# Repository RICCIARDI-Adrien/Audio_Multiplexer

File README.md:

# Audio multiplexer

## Description

A simple passive multiplexer providing :
* two 3.5mm jack inputs connected to two PC line outputs,
* two 3.5mm jack outputs connected to active speakers and a headset,
* one 3.5mm jack input connected to the headset microphone,
* two 3.5mm jack outputs connected to two PC microphone inputs.

```
                      +------+
             Line out |      | Mic in
     +----------------| PC 1 |<---------------+
     |                |      |                |
     |                +------+                |
     |                                        |
     |                +------+                |
     |       Line out |      | Mic in         |
     |   +------------| PC 2 |<-----------+   |
     |   |            |      |            |   |
     |   |            +------+            |   |
     |   |                                |   |
     v   v                                |   |
  +----------------------------------------------+             
  |              AUDIO MULTIPLEXER               |
  |                                              |
  |  Audio             Audio                Mic  |
  |   in                out                 in   |
  |                                              |
  +----------------------------------------------+
                       |  |                  ^
                       |  |                  |
                +------+  +-----+   +--------+
                |               |   |
                v               v   |
           +----------+      +---------+
           |          |      | Headset |
           | Speakers |      |  with   |
           |          |      |  mic    |
           +----------+      +---------+
```

The multiplexer microphone input is designed to be driven separately in case this is needed later.

## PCB

The PCB has been designed with KiCad 6.0.6.

Naked PCB :

Assembled PCB :

## Casing

The casing has been designed with FreeCAD 0.19. The multiple DXF files generated by FreeCAD have been combined using LibreCAD 2.1.3.
The casing has been designed to be laser-cut in a 4-mm thick 304 stainless steel.

Steel plates :

Casing top :

Casing bottom :

Casing front :

Casing rear :

Casing front angled :

Casing rear angled :

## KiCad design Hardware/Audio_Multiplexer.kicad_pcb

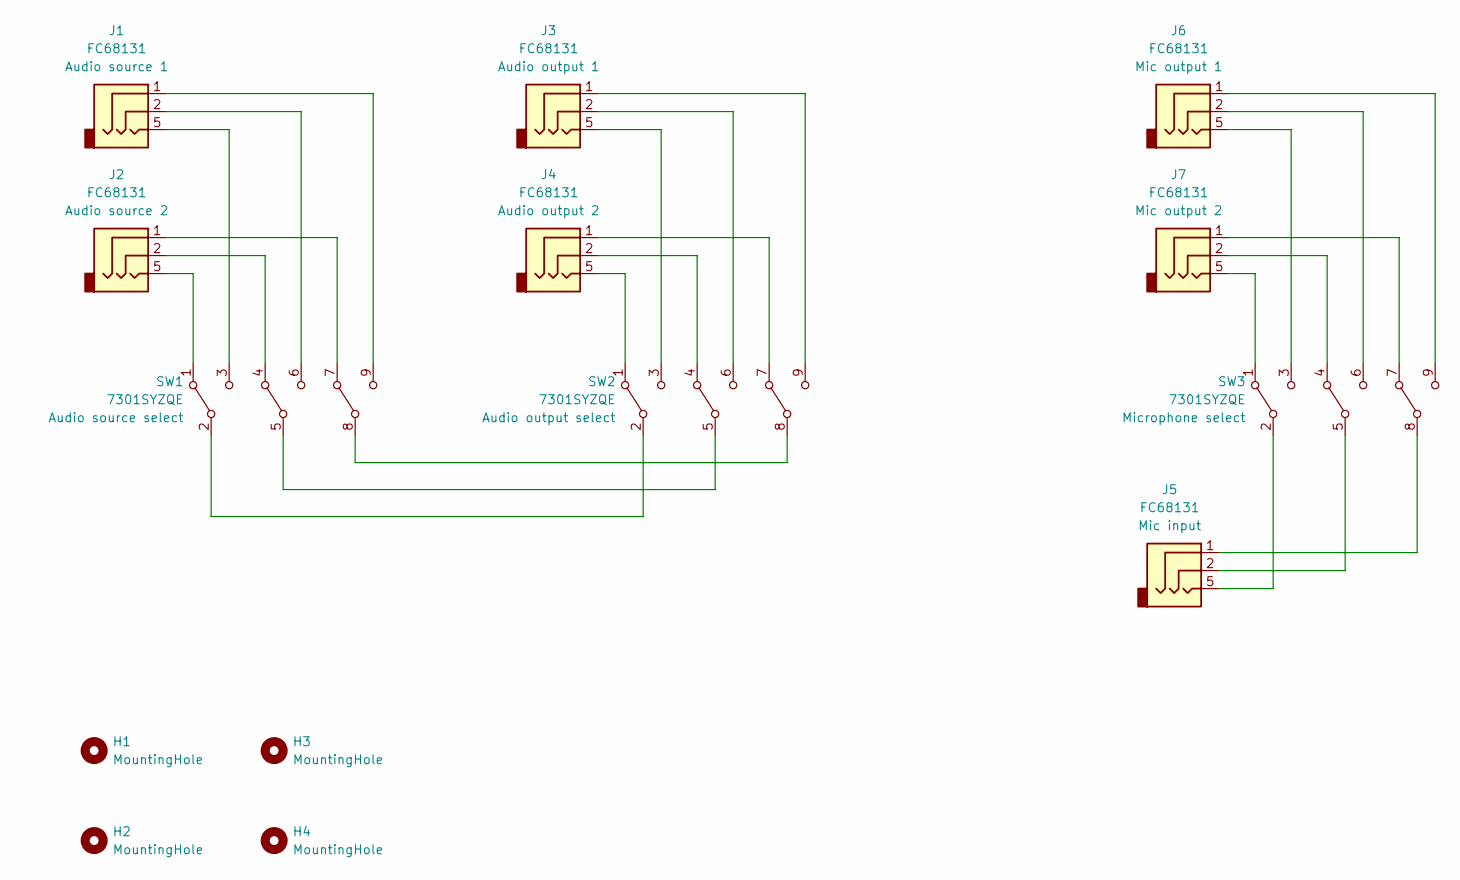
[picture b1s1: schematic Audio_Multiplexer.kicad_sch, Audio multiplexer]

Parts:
H1, H2, H3, H4: MountingHole; MountingHole_4.5mm
J1, J2, J3, J4, J5, J6, J7: FC68131
SW1, SW2, SW3: 7301SYZQE

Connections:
unnamed: J1.1, SW1.9
unnamed: J1.2, SW1.6
unnamed: J1.5, SW1.3
unnamed: J2.1, SW1.7
unnamed: J2.2, SW1.4
unnamed: J2.5, SW1.1
unnamed: J3.1, SW2.9
unnamed: J3.2, SW2.6
unnamed: J3.5, SW2.3
unnamed: J4.1, SW2.7
unnamed: J4.2, SW2.4
unnamed: J4.5, SW2.1
unnamed: J5.1, SW3.8
unnamed: J5.2, SW3.5
unnamed: J5.5, SW3.2
unnamed: J6.1, SW3.9
unnamed: J6.2, SW3.6
unnamed: J6.5, SW3.3
unnamed: J7.1, SW3.7
unnamed: J7.2, SW3.4
unnamed: J7.5, SW3.1
unnamed: SW1.2, SW2.2
unnamed: SW1.5, SW2.5
unnamed: SW1.8, SW2.8

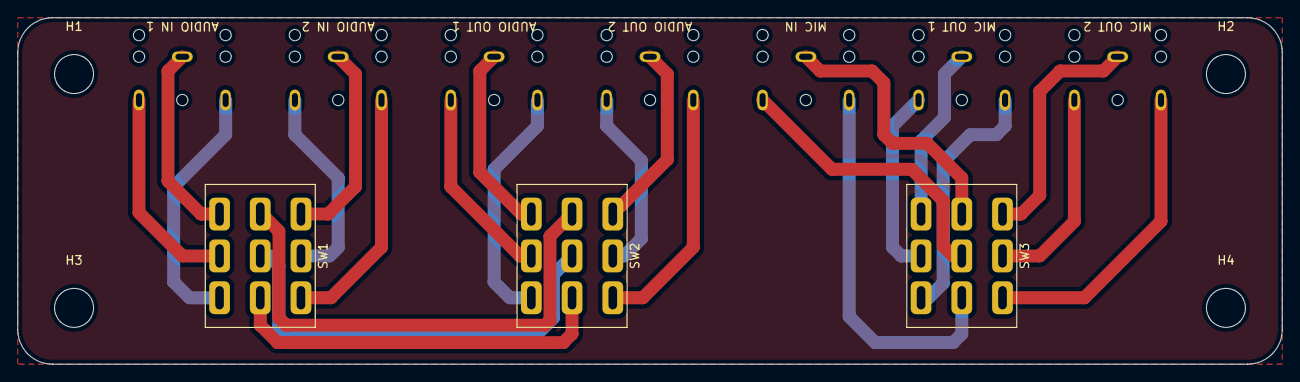
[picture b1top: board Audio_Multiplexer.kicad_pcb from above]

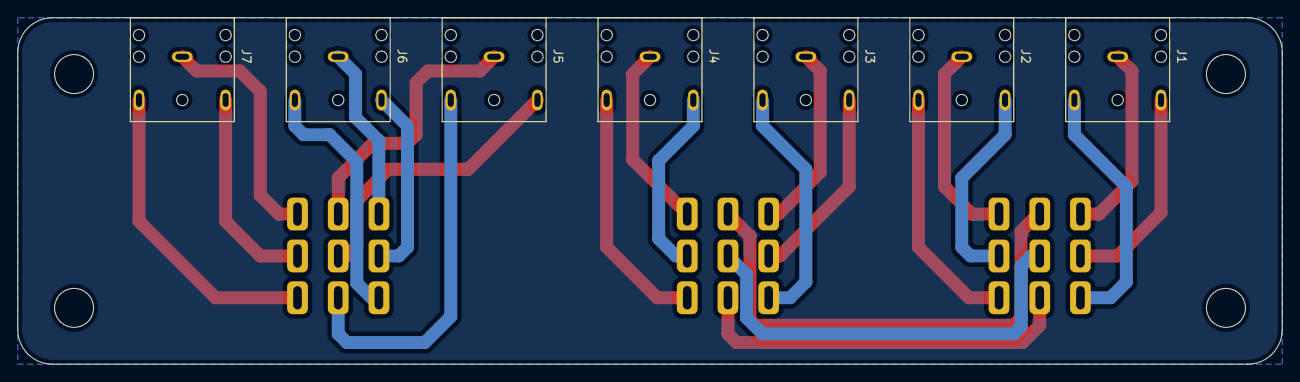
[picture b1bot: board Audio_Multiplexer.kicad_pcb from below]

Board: 2 copper layers, 146.0 x 40.0 mm, 14 parts (7 on the bottom side), 24 nets.

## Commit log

2022-07-15 Initial commit. Added README.md.
2022-07-15 Added MIT license.
2022-07-15 Started schematic. Added FC68131 audio jack symbol, footprint and 3D model.
2022-07-15 Added 7301SYZQE switch symbol, footprint and 3D model.
2022-07-15 Finished schematic. Added audio and microphone blocks.
2022-07-15 Placed all components and routed the circuit.
2022-07-15 Rounded PCB corners to make them more robust.
2022-07-15 Added copper planes to PCB top and bottom layers in order to decrease the amount of copper to remove. This simplifies the PCB manufacturing process.
2022-07-15 Added jack connectors label silkscreen texts to the PCB. Also added the design date.
2022-07-15 Set PCB grid origin and drill grid origin.
2022-07-17 Decreased PCB width by one millimeter so the casing can be 2 millimeters large on each side.
2022-07-17 Started casing design. Added a generic plate sketch.
2022-07-31 Improved a PCB trace to make it more straight.
2022-08-01 Finished casing top plate.
2022-08-07 Added the hex standoff model to the casing.
2022-08-07 Aligned casing bottom plate.
2022-08-07 Aligned casing top plate with PCB.
2022-08-07 Added all casing hex standoffs and aligned them.
2022-08-15 Added the PCB fixation holes to the casing bottom plate.
2022-08-15 Added top plate and bottom plate casing drawings to be able to export them as DXF.
2022-08-15 Improved casing top plate sketch and increased its length and width by 2mm each to be able to cut the plate in 4-mm thick steel with a laser.
2022-08-15 Improved casing bottom plate sketch and increased its length and width by 2mm each to be able to cut the plate in 4-mm thick steel with a laser.
2022-08-15 Added PCB and casing information to the README.md. Also added naked PCB and assembled PCB pictures.
2022-08-22 Added casing pictures to the README.md.
